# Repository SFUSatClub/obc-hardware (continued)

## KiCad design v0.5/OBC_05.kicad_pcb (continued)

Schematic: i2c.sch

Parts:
R10, R11: 10k; R_0402
U1: TMS570LS0714; LQFP-144_20x20mm_Pitch0.5mm

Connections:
1v2: U1.17, U1.29, U1.45, U1.48, U1.49, U1.57, U1.87, U1.101, U1.114, U1.123, U1.137, U1.143; also elsewhere on the board
3v3: R10.1, R11.1, U1.10, U1.26, U1.42, U1.66, U1.69, U1.104, U1.120, U1.134, U1.136; also elsewhere on the board
/MCU_Support_Reset/OSC_N: U1.20; also elsewhere on the board
/MCU_Support_Reset/OSC_P: U1.18; also elsewhere on the board
AD1_11: U1.75
AD1_12: U1.77
AD1_13: U1.79
AD1_14: U1.82
AD1_15: U1.85
AD1_16: U1.58
AD1_17: U1.59; also elsewhere on the board
AD1_18: U1.62; also elsewhere on the board
AD1_19: U1.63; also elsewhere on the board
AD1_20: U1.64; also elsewhere on the board
AD1_21: U1.65
AD1_22: U1.81
AD1_23: U1.84
FLASH0_CS: U1.105; also elsewhere on the board
FLASH1_CS: U1.130; also elsewhere on the board
FLASH2_CS: U1.40; also elsewhere on the board
FLASH_CLK: U1.95; also elsewhere on the board
FLASH_MISO: U1.94; also elsewhere on the board
FLASH_MOSI: U1.93; also elsewhere on the board
GIOA0: U1.2; also elsewhere on the board
GIOA1: U1.5; also elsewhere on the board
GIOA2: U1.9; also elsewhere on the board
GIOA6: U1.16; also elsewhere on the board
GIOB1: U1.133; also elsewhere on the board
GIOB2: U1.142; also elsewhere on the board
GIOB3: U1.1; also elsewhere on the board
GND: U1.11, U1.21, U1.27, U1.28, U1.34, U1.43, U1.44, U1.47, U1.50, U1.56, U1.67, U1.68, U1.88, U1.102, U1.103, U1.115, U1.121, U1.122, U1.135, U1.138, U1.144; also elsewhere on the board
I2C_SCL: R11.2, U1.3; also elsewhere on the board
I2C_SDA: R10.2, U1.4; also elsewhere on the board
INA_OUT: U1.73; also elsewhere on the board
LIN_RX: U1.131; also elsewhere on the board
LIN_TX: U1.132; also elsewhere on the board
MASTER_RESET: U1.46; also elsewhere on the board
unnamed 43: U1.19; also elsewhere on the board
unnamed 46: U1.116; also elsewhere on the board
unnamed 104: U1.55; also elsewhere on the board
unnamed 115: U1.86; also elsewhere on the board
RF_CLK: U1.53; also elsewhere on the board
RF_CS: U1.37; also elsewhere on the board
RF_CS2: U1.6; also elsewhere on the board
RF_IRQ: U1.14; also elsewhere on the board
RF_MISO: U1.51; also elsewhere on the board
RF_MOSI: U1.52; also elsewhere on the board
RTCK: U1.113
RTC_CLK: U1.100; also elsewhere on the board
RTC_CS: U1.32; also elsewhere on the board
RTC_MISO: U1.98; also elsewhere on the board
RTC_MOSI: U1.99; also elsewhere on the board
TCK: U1.112; also elsewhere on the board
TDI: U1.110; also elsewhere on the board
TDO: U1.111; also elsewhere on the board
TMS: U1.108; also elsewhere on the board
UART_RX: U1.38; also elsewhere on the board
UART_TX: U1.39; also elsewhere on the board
WATCHDOG: U1.126; also elsewhere on the board
nERROR: U1.117; also elsewhere on the board
nTRST: U1.109; also elsewhere on the board
xGPIO0: U1.23; also elsewhere on the board
xGPIO1: U1.30; also elsewhere on the board
xGPIO2: U1.31; also elsewhere on the board
xGPIO3: U1.97; also elsewhere on the board
xGPIO4: U1.96; also elsewhere on the board
xGPIO5: U1.91; also elsewhere on the board
xGPIO6: U1.41; also elsewhere on the board
xGPIO7: U1.22; also elsewhere on the board
xGPIO8: U1.106; also elsewhere on the board
xGPIO9: U1.90; also elsewhere on the board
xGPIO10: U1.89; also elsewhere on the board
xGPIO11: U1.129; also elsewhere on the board
xGPIO12: U1.128; also elsewhere on the board
xNHET0: U1.15; also elsewhere on the board
xNHET1: U1.92; also elsewhere on the board

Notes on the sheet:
I2C pullup resistor values are hotly contested. Temp sensor datasheet says 10k, this has been tested and works with 0.4. May need to adjust once more devices are on the bus.

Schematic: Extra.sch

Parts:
U1: TMS570LS0714; LQFP-144_20x20mm_Pitch0.5mm

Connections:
1v2: U1.17, U1.29, U1.45, U1.48, U1.49, U1.57, U1.87, U1.101, U1.114, U1.123, U1.137, U1.143; also elsewhere on the board
3v3: U1.10, U1.26, U1.42, U1.66, U1.69, U1.104, U1.120, U1.134, U1.136; also elsewhere on the board
/MCU_Support_Reset/OSC_N: U1.20; also elsewhere on the board
/MCU_Support_Reset/OSC_P: U1.18; also elsewhere on the board
AD1_11: U1.75
AD1_12: U1.77
AD1_13: U1.79
AD1_14: U1.82
AD1_15: U1.85
AD1_16: U1.58
AD1_17: U1.59; also elsewhere on the board
AD1_18: U1.62; also elsewhere on the board
AD1_19: U1.63; also elsewhere on the board
AD1_20: U1.64; also elsewhere on the board
AD1_21: U1.65
AD1_22: U1.81
AD1_23: U1.84
FLASH0_CS: U1.105; also elsewhere on the board
FLASH1_CS: U1.130; also elsewhere on the board
FLASH2_CS: U1.40; also elsewhere on the board
FLASH_CLK: U1.95; also elsewhere on the board
FLASH_MISO: U1.94; also elsewhere on the board
FLASH_MOSI: U1.93; also elsewhere on the board
GIOA0: U1.2; also elsewhere on the board
GIOA1: U1.5; also elsewhere on the board
GIOA2: U1.9; also elsewhere on the board
GIOA6: U1.16; also elsewhere on the board
GIOB1: U1.133; also elsewhere on the board
GIOB2: U1.142; also elsewhere on the board
GIOB3: U1.1; also elsewhere on the board
GND: U1.11, U1.21, U1.27, U1.28, U1.34, U1.43, U1.44, U1.47, U1.50, U1.56, U1.67, U1.68, U1.88, U1.102, U1.103, U1.115, U1.121, U1.122, U1.135, U1.138, U1.144; also elsewhere on the board
I2C_SCL: U1.3; also elsewhere on the board
I2C_SDA: U1.4; also elsewhere on the board
INA_OUT: U1.73; also elsewhere on the board
LIN_RX: U1.131; also elsewhere on the board
LIN_TX: U1.132; also elsewhere on the board
MASTER_RESET: U1.46; also elsewhere on the board
unnamed 43: U1.19; also elsewhere on the board
unnamed 46: U1.116; also elsewhere on the board
unnamed 104: U1.55; also elsewhere on the board
unnamed 115: U1.86; also elsewhere on the board
RF_CLK: U1.53; also elsewhere on the board
RF_CS: U1.37; also elsewhere on the board
RF_CS2: U1.6; also elsewhere on the board
RF_IRQ: U1.14; also elsewhere on the board
RF_MISO: U1.51; also elsewhere on the board
RF_MOSI: U1.52; also elsewhere on the board
RTCK: U1.113
RTC_CLK: U1.100; also elsewhere on the board
RTC_CS: U1.32; also elsewhere on the board
RTC_MISO: U1.98; also elsewhere on the board
RTC_MOSI: U1.99; also elsewhere on the board
TCK: U1.112; also elsewhere on the board
TDI: U1.110; also elsewhere on the board
TDO: U1.111; also elsewhere on the board
TMS: U1.108; also elsewhere on the board
UART_RX: U1.38; also elsewhere on the board
UART_TX: U1.39; also elsewhere on the board
WATCHDOG: U1.126; also elsewhere on the board
nERROR: U1.117; also elsewhere on the board
nTRST: U1.109; also elsewhere on the board
xGPIO0: U1.23; also elsewhere on the board
xGPIO1: U1.30; also elsewhere on the board
xGPIO2: U1.31; also elsewhere on the board
xGPIO3: U1.97; also elsewhere on the board
xGPIO4: U1.96; also elsewhere on the board
xGPIO5: U1.91; also elsewhere on the board
xGPIO6: U1.41; also elsewhere on the board
xGPIO7: U1.22; also elsewhere on the board
xGPIO8: U1.106; also elsewhere on the board
xGPIO9: U1.90; also elsewhere on the board
xGPIO10: U1.89; also elsewhere on the board
xGPIO11: U1.129; also elsewhere on the board
xGPIO12: U1.128; also elsewhere on the board
xNHET0: U1.15; also elsewhere on the board
xNHET1: U1.92; also elsewhere on the board

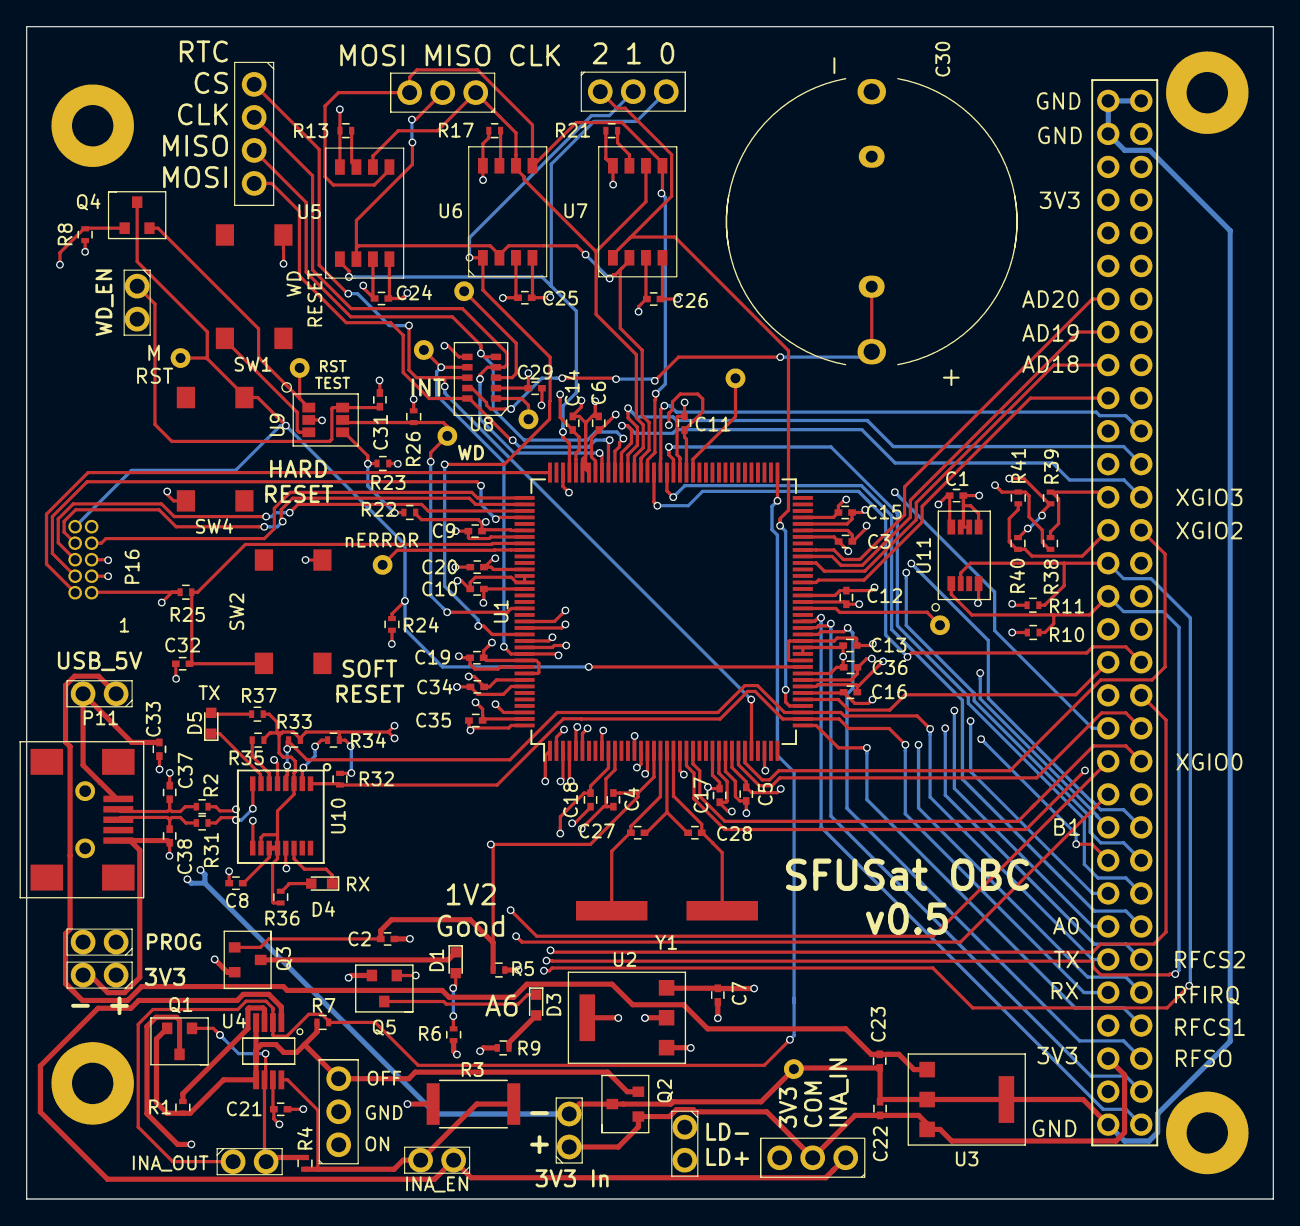
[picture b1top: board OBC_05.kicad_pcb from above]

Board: 4 copper layers, 95.9 x 90.2 mm, 118 parts (0 on the bottom side), 103 nets.

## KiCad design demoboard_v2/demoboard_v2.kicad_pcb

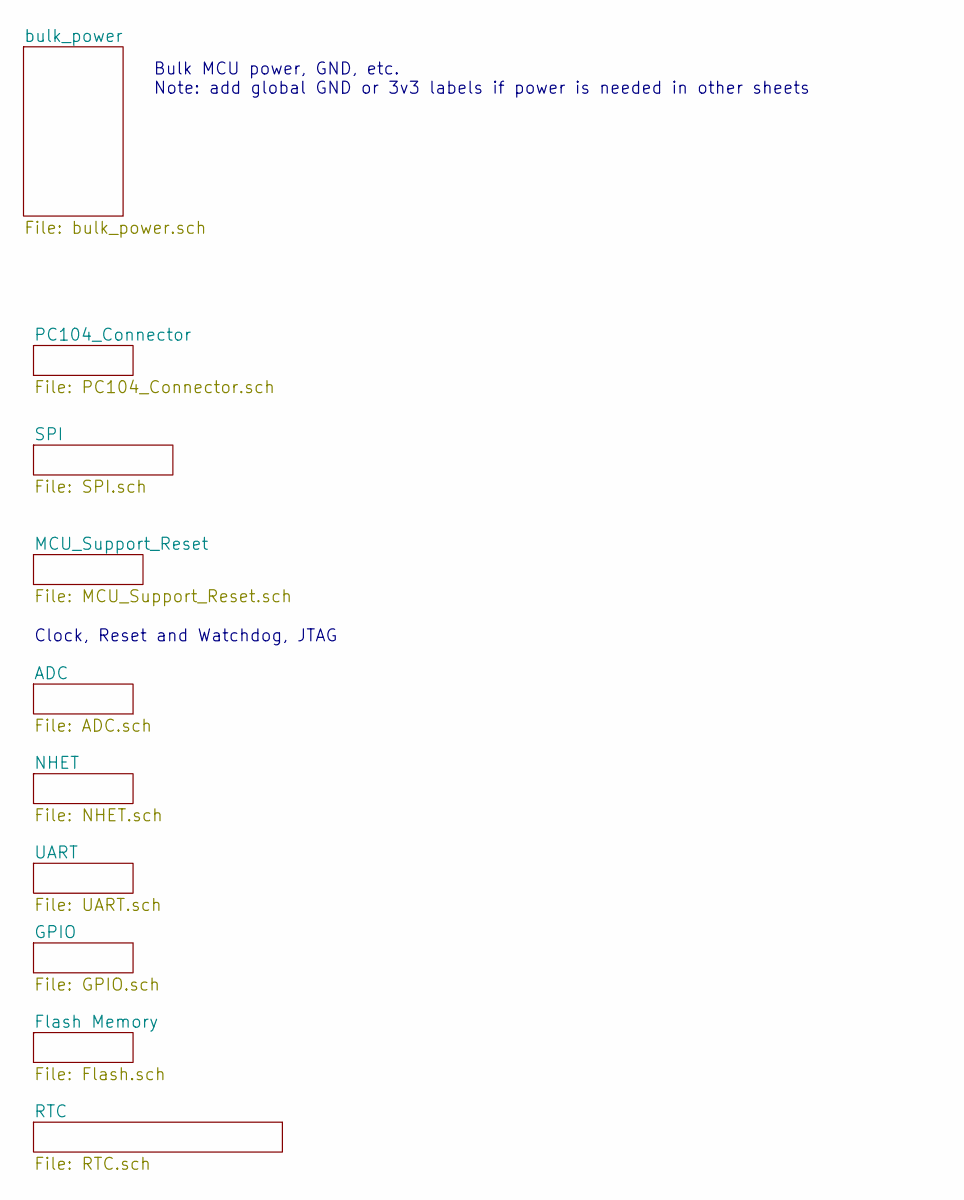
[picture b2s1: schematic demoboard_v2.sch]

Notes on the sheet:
Clock, Reset and Watchdog, JTAG
Bulk MCU power, GND, etc. Note: add global GND or 3v3 labels if power is needed in other sheets

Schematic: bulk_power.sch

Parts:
C2: 1uF; C_0402
C4, C5, C6, C7, C9, C10, C11, C12, C13, C14, C15, C16, C17, C18, C19, C20: 0.1µF; C_0402
C21, C23: 1µF; C_0402
C22: 4.7µF; C_0402
D1: LED; LED_0603
P1: 3v3_IN_CONNECTOR; 2x01In_Header_v2
P2: INA_INPUT; 3x_01In_Header_v2
P3: INA_GND; 3x_01In_Header_v2
P4: INA_EN; 2x01In_Header_v2
P5: INA_OUTPUT; 2x01In_Header_v2
Q1, Q2: DMN2075U; SOT23_DMN2075U
Q3: 1v2_GOOD; SOT23_DMN2075U
R1: 2k; R_0402
R2, R4: 10k; R_0402
R3: 0.04; R_2512
R5: 10K; R_0402
R6: 100; R_0402
U1: TMS570LS0714; LQFP-144_20x20mm_Pitch0.5mm
U2: AP7331; SOT25
U3: AP7361_3.3v; SOT-223
U4: INA301; VSSOP_8

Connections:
1v2: C2.1, C4.1, C5.1, C6.1, C7.1, C9.1, C10.1, C11.1, C12.1, C13.1, Q3.2 (G), R5.1, U1.17, U1.29, U1.45, U1.48, U1.49, U1.57, U1.87, U1.101, U1.114, U1.123, U1.137, U1.143, U2.5 (OUT); also elsewhere on the board
3v3: C14.2, C15.1, C16.1, C17.2, C18.1, C19.1, C20.1, C21.1, P1.1, P2.3, Q2.2 (G), R3.2, R6.1, U1.10, U1.26, U1.42, U1.66, U1.69, U1.104, U1.120, U1.134, U1.136, U2.1 (IN), U2.3 (EN), U4.7 (IN-); also elsewhere on the board
3v3_OUTPUT: C22.1, P2.2, U3.3
5v0: C23.1, U3.1; also elsewhere on the board
104_GND: C22.2, C23.2, P3.3, Q1.3 (S), R2.2, U3.2, U3.4, U4.4 (GND), U4.5 (RESET); also elsewhere on the board
AD1_3: U1.74; also elsewhere on the board
AD1_4: U1.76; also elsewhere on the board
AD1_5: U1.78; also elsewhere on the board
AD1_6: U1.80; also elsewhere on the board
AD1_7: U1.61; also elsewhere on the board
AD1_8: U1.83; also elsewhere on the board
AD1_9: U1.70; also elsewhere on the board
AD1_10: U1.72; also elsewhere on the board
FLASH0_CS: U1.105; also elsewhere on the board
FLASH1_CS: U1.130; also elsewhere on the board
FLASH2_CS: U1.40; also elsewhere on the board
FLASH_CLK: U1.95; also elsewhere on the board
FLASH_MISO: U1.94; also elsewhere on the board
FLASH_MOSI: U1.93; also elsewhere on the board
GIOA0: U1.2; also elsewhere on the board
GIOA1: U1.5
GIOA2: U1.9
GIOA6: U1.16; also elsewhere on the board
GIOA7: U1.22
GIOB1: U1.133; also elsewhere on the board
GIOB2: U1.142; also elsewhere on the board
GIOB3: U1.1; also elsewhere on the board
GND: C2.2, C4.2, C5.2, C6.2, C7.2, C9.2, C10.2, C11.2, C12.2, C13.2, C14.1, C15.2, C16.2, C17.1, C18.2, C19.2, C20.2, C21.2, P3.2, Q2.3 (S), Q3.3 (S), R5.2, U1.11, U1.21, U1.27, U1.28, U1.34, U1.43, U1.44, U1.47, U1.50, U1.56, U1.67, U1.68, U1.88, U1.102, U1.103, U1.115, U1.121, U1.122, U1.135, U1.138, U1.144, U2.2 (GND); also elsewhere on the board
I2C_SCL: U1.3; also elsewhere on the board
I2C_SDA: U1.4; also elsewhere on the board
INA_ALERT: P5.2, Q1.2 (G), R4.2, U4.6 (ALERT)
INA_INPUT: P2.1, P4.1, U4.1 (VS)
INA_OUT: P5.1, U1.73, U4.2 (OUT); also elsewhere on the board
MASTER_RESET: U1.46; also elsewhere on the board
NHET1_4: U1.36; also elsewhere on the board
NHET1_7: U1.33; also elsewhere on the board
NHET1_22: U1.15; also elsewhere on the board
NHET1_26: U1.92; also elsewhere on the board
unnamed 40: U1.19; also elsewhere on the board
unnamed 41: U1.18; also elsewhere on the board
unnamed 42: U1.20; also elsewhere on the board
unnamed 44: U1.116; also elsewhere on the board
unnamed: D1.1, Q3.1 (D)
unnamed: D1.2, R6.2
unnamed: P1.2, Q2.1 (D)
unnamed: P3.1, Q1.1 (D)
unnamed: P4.2, R3.1, R4.1, U4.8 (IN+)
unnamed: R1.1, U4.3 (LIMIT)
unnamed: R1.2, R2.1
unnamed 86: U1.97; also elsewhere on the board
unnamed 93: U1.55; also elsewhere on the board
unnamed 107: U1.86; also elsewhere on the board
unnamed 112: U1.117; also elsewhere on the board
RF_ADC1: U1.60; also elsewhere on the board
RF_ADC2: U1.71; also elsewhere on the board
RF_CLK: U1.53; also elsewhere on the board
RF_CS: U1.37; also elsewhere on the board
RF_GAIN_CS: U1.6; also elsewhere on the board
RF_MISO: U1.51; also elsewhere on the board
RF_MOSI: U1.52; also elsewhere on the board
RF_PWM1: U1.140; also elsewhere on the board
RF_PWM2: U1.141; also elsewhere on the board
RTCK: U1.113; also elsewhere on the board
RTC_CLK: U1.25; also elsewhere on the board
RTC_CS: U1.24; also elsewhere on the board
RTC_MISO: U1.31; also elsewhere on the board
RTC_MOSI: U1.30; also elsewhere on the board
SPI5_CLK: U1.100; also elsewhere on the board
SPI5_CS0: U1.32; also elsewhere on the board
SPI5_MISO: U1.98; also elsewhere on the board
SPI5_MOSI: U1.99; also elsewhere on the board
TCK: U1.112; also elsewhere on the board
TDI: U1.110; also elsewhere on the board
TDO: U1.111; also elsewhere on the board
TMS: U1.108; also elsewhere on the board
UART_RX: U1.38; also elsewhere on the board
UART_TX: U1.39; also elsewhere on the board
WATCHDOG: U1.126; also elsewhere on the board
nTRST: U1.109; also elsewhere on the board

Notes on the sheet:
1.2v regulator
INA_POWER_ENABLE Short this connector if using INA Prevents INA from being powered when it is supposed to be disconnected
Use this connector to enable or disable INA control
2+3 closed: INA Disabled 2+1 closed: INA Enabled
reverse polarity fet
SEL Protection FET
C1, C3, C8 were removed at the board level, as multiple pins were connected to one cap.

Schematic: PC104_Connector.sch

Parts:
D2: PESD5Zx; PESD57zx
J1: PC104-8BIT; PC104-8bit
Q4: DMN2075U; SOT23_DMN2075U

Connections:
5v0: D2.1 (c), J1.3B, J1.29B, Q4.2 (G); also elsewhere on the board
104_GND: Q4.3 (S); also elsewhere on the board
104_In_GND: D2.2 (a), J1.1B, J1.31B, J1.32A, J1.32B, Q4.1 (D)
AD1_3: J1.19A; also elsewhere on the board
AD1_4: J1.20A; also elsewhere on the board
AD1_5: J1.21A; also elsewhere on the board
AD1_6: J1.22A; also elsewhere on the board
AD1_7: J1.23A; also elsewhere on the board
AD1_8: J1.24A; also elsewhere on the board
AD1_9: J1.25A; also elsewhere on the board
AD1_10: J1.26A; also elsewhere on the board
ANTENNA_DEPLOY: J1.7A
GIOA0: J1.7B; also elsewhere on the board
GIOB1: J1.8B; also elsewhere on the board
GIOB2: J1.11B; also elsewhere on the board
GIOB3: J1.12B; also elsewhere on the board
I2C_SCL: J1.18B; also elsewhere on the board
I2C_SDA: J1.17B; also elsewhere on the board
NHET1_4: J1.19B; also elsewhere on the board
NHET1_7: J1.20B; also elsewhere on the board
NHET1_22: J1.21B; also elsewhere on the board
NHET1_26: J1.22B; also elsewhere on the board
RF_ADC1: J1.8A; also elsewhere on the board
RF_ADC2: J1.9A; also elsewhere on the board
RF_CLK: J1.1A; also elsewhere on the board
RF_CS: J1.4A; also elsewhere on the board
RF_GAIN_CS: J1.6A; also elsewhere on the board
RF_IRQ: J1.5A
RF_MISO: J1.3A; also elsewhere on the board
RF_MOSI: J1.2A; also elsewhere on the board
RF_PWM1: J1.10A; also elsewhere on the board
RF_PWM2: J1.11A; also elsewhere on the board
SPI5_CLK: J1.16A; also elsewhere on the board
SPI5_CS0: J1.17A; also elsewhere on the board
SPI5_MISO: J1.14A; also elsewhere on the board
SPI5_MOSI: J1.15A; also elsewhere on the board
UART_RX: J1.5B; also elsewhere on the board
UART_TX: J1.6B; also elsewhere on the board

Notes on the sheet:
Global Power Needed to connect power on the different sheets
Grounding: 104_GND is connected either to "GND" net directly, or to GND net through the FET, allowing the load to be switched by the SEL mitigation circuit. This is selected by a jumper on the power page.
5v reverse polarity FET

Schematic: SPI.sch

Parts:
U1: TMS570LS0714; LQFP-144_20x20mm_Pitch0.5mm

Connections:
1v2: U1.17, U1.29, U1.45, U1.48, U1.49, U1.57, U1.87, U1.101, U1.114, U1.123, U1.137, U1.143; also elsewhere on the board
3v3: U1.10, U1.26, U1.42, U1.66, U1.69, U1.104, U1.120, U1.134, U1.136; also elsewhere on the board
AD1_3: U1.74; also elsewhere on the board
AD1_4: U1.76; also elsewhere on the board
AD1_5: U1.78; also elsewhere on the board
AD1_6: U1.80; also elsewhere on the board
AD1_7: U1.61; also elsewhere on the board
AD1_8: U1.83; also elsewhere on the board
AD1_9: U1.70; also elsewhere on the board
AD1_10: U1.72; also elsewhere on the board
FLASH0_CS: U1.105; also elsewhere on the board
FLASH1_CS: U1.130; also elsewhere on the board
FLASH2_CS: U1.40; also elsewhere on the board
FLASH_CLK: U1.95; also elsewhere on the board
FLASH_MISO: U1.94; also elsewhere on the board
FLASH_MOSI: U1.93; also elsewhere on the board
GIOA0: U1.2; also elsewhere on the board
GIOA1: U1.5
GIOA2: U1.9
GIOA6: U1.16; also elsewhere on the board
GIOA7: U1.22
GIOB1: U1.133; also elsewhere on the board
GIOB2: U1.142; also elsewhere on the board
GIOB3: U1.1; also elsewhere on the board
GND: U1.11, U1.21, U1.27, U1.28, U1.34, U1.43, U1.44, U1.47, U1.50, U1.56, U1.67, U1.68, U1.88, U1.102, U1.103, U1.115, U1.121, U1.122, U1.135, U1.138, U1.144; also elsewhere on the board
I2C_SCL: U1.3; also elsewhere on the board
I2C_SDA: U1.4; also elsewhere on the board
INA_OUT: U1.73; also elsewhere on the board
MASTER_RESET: U1.46; also elsewhere on the board
NHET1_4: U1.36; also elsewhere on the board
NHET1_7: U1.33; also elsewhere on the board
NHET1_22: U1.15; also elsewhere on the board
NHET1_26: U1.92; also elsewhere on the board
unnamed 40: U1.19; also elsewhere on the board
unnamed 41: U1.18; also elsewhere on the board
unnamed 42: U1.20; also elsewhere on the board
unnamed 44: U1.116; also elsewhere on the board
unnamed 86: U1.97; also elsewhere on the board
unnamed 93: U1.55; also elsewhere on the board
unnamed 107: U1.86; also elsewhere on the board
unnamed 112: U1.117; also elsewhere on the board
RF_ADC1: U1.60; also elsewhere on the board
RF_ADC2: U1.71; also elsewhere on the board
RF_CLK: U1.53; also elsewhere on the board
RF_CS: U1.37; also elsewhere on the board
RF_GAIN_CS: U1.6; also elsewhere on the board
RF_MISO: U1.51; also elsewhere on the board
RF_MOSI: U1.52; also elsewhere on the board
RF_PWM1: U1.140; also elsewhere on the board
RF_PWM2: U1.141; also elsewhere on the board
RTCK: U1.113; also elsewhere on the board
RTC_CLK: U1.25; also elsewhere on the board
RTC_CS: U1.24; also elsewhere on the board
RTC_MISO: U1.31; also elsewhere on the board
RTC_MOSI: U1.30; also elsewhere on the board
SPI5_CLK: U1.100; also elsewhere on the board
SPI5_CS0: U1.32; also elsewhere on the board
SPI5_MISO: U1.98; also elsewhere on the board
SPI5_MOSI: U1.99; also elsewhere on the board
TCK: U1.112; also elsewhere on the board
TDI: U1.110; also elsewhere on the board
TDO: U1.111; also elsewhere on the board
TMS: U1.108; also elsewhere on the board
UART_RX: U1.38; also elsewhere on the board
UART_TX: U1.39; also elsewhere on the board
WATCHDOG: U1.126; also elsewhere on the board
nTRST: U1.109; also elsewhere on the board

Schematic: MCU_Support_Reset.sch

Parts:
C27, C28: 33pF; C_0402
C31, C32: 0.1µF; C_0402
JTAG_5V_SRC1: JTAG_5V_SRC; 2x01In_Header_v2
P7: OSC_FUALT_INJECT; 2x01In_Header_v2
P12: JTAG_20PIN; JTAG_20pin
R22: 200k; R_0402
R23: 187k; R_0402
R24, R27, R28, R29, R30: 100k; R_0402
R25: 10k; R_0402
SW1, SW2: SPST; Tact_SW_SMD_v2
U1: TMS570LS0714; LQFP-144_20x20mm_Pitch0.5mm
U9: TPS3110; SOT_23_6
W12: nERROR; Test_Point
W14: RESET_TEST; Test_Point
Y1: XTAL; SMD_XTAL

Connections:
1v2: R22.1, U1.17, U1.29, U1.45, U1.48, U1.49, U1.57, U1.87, U1.101, U1.114, U1.123, U1.137, U1.143; also elsewhere on the board
3v3: C31.1, P12.1, R24.1, R25.1, R27.1, R28.1, R29.1, R30.1, U1.10, U1.26, U1.42, U1.66, U1.69, U1.104, U1.120, U1.134, U1.136, U9.6 (VDD); also elsewhere on the board
5v0: JTAG_5V_SRC1.2; also elsewhere on the board
AD1_3: U1.74; also elsewhere on the board
AD1_4: U1.76; also elsewhere on the board
AD1_5: U1.78; also elsewhere on the board
AD1_6: U1.80; also elsewhere on the board
AD1_7: U1.61; also elsewhere on the board
AD1_8: U1.83; also elsewhere on the board
AD1_9: U1.70; also elsewhere on the board
AD1_10: U1.72; also elsewhere on the board
FLASH0_CS: U1.105; also elsewhere on the board
FLASH1_CS: U1.130; also elsewhere on the board
FLASH2_CS: U1.40; also elsewhere on the board
FLASH_CLK: U1.95; also elsewhere on the board
FLASH_MISO: U1.94; also elsewhere on the board
FLASH_MOSI: U1.93; also elsewhere on the board
GIOA0: U1.2; also elsewhere on the board
GIOA1: U1.5
GIOA2: U1.9
GIOA6: U1.16; also elsewhere on the board
GIOA7: U1.22
GIOB1: U1.133; also elsewhere on the board
GIOB2: U1.142; also elsewhere on the board
GIOB3: U1.1; also elsewhere on the board
GND: C31.2, C32.2, P7.1, P12.4, P12.6, P12.8, P12.10, P12.12, P12.14, P12.16, P12.18, P12.20, R23.2, SW1.2, SW2.2, U1.11, U1.21, U1.27, U1.28, U1.34, U1.43, U1.44, U1.47, U1.50, U1.56, U1.67, U1.68, U1.88, U1.102, U1.103, U1.115, U1.121, U1.122, U1.135, U1.138, U1.144, U9.2 (GND); also elsewhere on the board
I2C_SCL: U1.3; also elsewhere on the board
I2C_SDA: U1.4; also elsewhere on the board
INA_OUT: U1.73; also elsewhere on the board
MASTER_RESET: R24.2, U1.46, U9.1 (RESET), W14.1; also elsewhere on the board
NHET1_4: U1.36; also elsewhere on the board
NHET1_7: U1.33; also elsewhere on the board
NHET1_22: U1.15; also elsewhere on the board
NHET1_26: U1.92; also elsewhere on the board
unnamed: C27.1, C28.1, P7.2, U1.19, Y1.1, Y1.2
unnamed: C27.2, U1.18
unnamed: C28.2, U1.20
unnamed: C32.1, R25.2, SW2.1, U1.116
unnamed: JTAG_5V_SRC1.1, P12.19
unnamed: R22.2, R23.1, U9.4 (SENSE)
unnamed 86: U1.97; also elsewhere on the board
unnamed: SW1.1, U9.3 (MR)
unnamed 93: U1.55; also elsewhere on the board
unnamed 107: U1.86; also elsewhere on the board
unnamed: U1.117, W12.1
RF_ADC1: U1.60; also elsewhere on the board
RF_ADC2: U1.71; also elsewhere on the board
RF_CLK: U1.53; also elsewhere on the board
RF_CS: U1.37; also elsewhere on the board
RF_GAIN_CS: U1.6; also elsewhere on the board
RF_MISO: U1.51; also elsewhere on the board
RF_MOSI: U1.52; also elsewhere on the board
RF_PWM1: U1.140; also elsewhere on the board
RF_PWM2: U1.141; also elsewhere on the board
RTCK: P12.11, R28.2, U1.113
RTC_CLK: U1.25; also elsewhere on the board
RTC_CS: U1.24; also elsewhere on the board
RTC_MISO: U1.31; also elsewhere on the board
RTC_MOSI: U1.30; also elsewhere on the board
SPI5_CLK: U1.100; also elsewhere on the board
SPI5_CS0: U1.32; also elsewhere on the board
SPI5_MISO: U1.98; also elsewhere on the board
SPI5_MOSI: U1.99; also elsewhere on the board
TCK: P12.9, R27.2, U1.112
TDI: P12.5, R29.2, U1.110
TDO: P12.13, U1.111
TMS: P12.7, R30.2, U1.108
UART_RX: U1.38; also elsewhere on the board
UART_TX: U1.39; also elsewhere on the board
WATCHDOG: U1.126, U9.5 (WDI); also elsewhere on the board
nTRST: P12.3, U1.109

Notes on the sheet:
nPORRST is hard reset
Soft Reset
Hard reset switch.

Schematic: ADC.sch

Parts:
R7: 10k; R_0402
U1: TMS570LS0714; LQFP-144_20x20mm_Pitch0.5mm
W7: AD1EVT1; Test_Point
W8: GIOB2; Test_Point

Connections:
1v2: U1.17, U1.29, U1.45, U1.48, U1.49, U1.57, U1.87, U1.101, U1.114, U1.123, U1.137, U1.143; also elsewhere on the board
3v3: U1.10, U1.26, U1.42, U1.66, U1.69, U1.104, U1.120, U1.134, U1.136; also elsewhere on the board
104_GND: R7.2; also elsewhere on the board
AD1_3: U1.74; also elsewhere on the board
AD1_4: U1.76; also elsewhere on the board
AD1_5: U1.78; also elsewhere on the board
AD1_6: U1.80; also elsewhere on the board
AD1_7: U1.61; also elsewhere on the board
AD1_8: U1.83; also elsewhere on the board
AD1_9: U1.70; also elsewhere on the board
AD1_10: U1.72; also elsewhere on the board
FLASH0_CS: U1.105; also elsewhere on the board
FLASH1_CS: U1.130; also elsewhere on the board
FLASH2_CS: U1.40; also elsewhere on the board
FLASH_CLK: U1.95; also elsewhere on the board
FLASH_MISO: U1.94; also elsewhere on the board
FLASH_MOSI: U1.93; also elsewhere on the board
GIOA0: U1.2; also elsewhere on the board
GIOA1: U1.5
GIOA2: U1.9
GIOA6: U1.16; also elsewhere on the board
GIOA7: U1.22
GIOB1: U1.133; also elsewhere on the board
GIOB2: U1.142; also elsewhere on the board
GIOB3: U1.1; also elsewhere on the board
GND: U1.11, U1.21, U1.27, U1.28, U1.34, U1.43, U1.44, U1.47, U1.50, U1.56, U1.67, U1.68, U1.88, U1.102, U1.103, U1.115, U1.121, U1.122, U1.135, U1.138, U1.144; also elsewhere on the board
I2C_SCL: U1.3; also elsewhere on the board
I2C_SDA: U1.4; also elsewhere on the board
INA_OUT: R7.1, U1.73; also elsewhere on the board
MASTER_RESET: U1.46; also elsewhere on the board
NHET1_4: U1.36; also elsewhere on the board
NHET1_7: U1.33; also elsewhere on the board
NHET1_22: U1.15; also elsewhere on the board
NHET1_26: U1.92; also elsewhere on the board
unnamed 40: U1.19; also elsewhere on the board
unnamed 41: U1.18; also elsewhere on the board
unnamed 42: U1.20; also elsewhere on the board
unnamed 44: U1.116; also elsewhere on the board
unnamed 86: U1.97; also elsewhere on the board
unnamed: U1.55, W8.1
unnamed: U1.86, W7.1
unnamed 112: U1.117; also elsewhere on the board
RF_ADC1: U1.60; also elsewhere on the board
RF_ADC2: U1.71; also elsewhere on the board
RF_CLK: U1.53; also elsewhere on the board
RF_CS: U1.37; also elsewhere on the board
RF_GAIN_CS: U1.6; also elsewhere on the board
RF_MISO: U1.51; also elsewhere on the board
RF_MOSI: U1.52; also elsewhere on the board
RF_PWM1: U1.140; also elsewhere on the board
RF_PWM2: U1.141; also elsewhere on the board
RTCK: U1.113; also elsewhere on the board
RTC_CLK: U1.25; also elsewhere on the board
RTC_CS: U1.24; also elsewhere on the board
RTC_MISO: U1.31; also elsewhere on the board
RTC_MOSI: U1.30; also elsewhere on the board
SPI5_CLK: U1.100; also elsewhere on the board
SPI5_CS0: U1.32; also elsewhere on the board
SPI5_MISO: U1.98; also elsewhere on the board
SPI5_MOSI: U1.99; also elsewhere on the board
TCK: U1.112; also elsewhere on the board
TDI: U1.110; also elsewhere on the board
TDO: U1.111; also elsewhere on the board
TMS: U1.108; also elsewhere on the board
UART_RX: U1.38; also elsewhere on the board
UART_TX: U1.39; also elsewhere on the board
WATCHDOG: U1.126; also elsewhere on the board
nTRST: U1.109; also elsewhere on the board

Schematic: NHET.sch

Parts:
U1: TMS570LS0714; LQFP-144_20x20mm_Pitch0.5mm

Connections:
1v2: U1.17, U1.29, U1.45, U1.48, U1.49, U1.57, U1.87, U1.101, U1.114, U1.123, U1.137, U1.143; also elsewhere on the board
3v3: U1.10, U1.26, U1.42, U1.66, U1.69, U1.104, U1.120, U1.134, U1.136; also elsewhere on the board
AD1_3: U1.74; also elsewhere on the board
AD1_4: U1.76; also elsewhere on the board
AD1_5: U1.78; also elsewhere on the board
AD1_6: U1.80; also elsewhere on the board
AD1_7: U1.61; also elsewhere on the board
AD1_8: U1.83; also elsewhere on the board
AD1_9: U1.70; also elsewhere on the board
AD1_10: U1.72; also elsewhere on the board
FLASH0_CS: U1.105; also elsewhere on the board
FLASH1_CS: U1.130; also elsewhere on the board
FLASH2_CS: U1.40; also elsewhere on the board
FLASH_CLK: U1.95; also elsewhere on the board
FLASH_MISO: U1.94; also elsewhere on the board
FLASH_MOSI: U1.93; also elsewhere on the board
GIOA0: U1.2; also elsewhere on the board
GIOA1: U1.5
GIOA2: U1.9
GIOA6: U1.16; also elsewhere on the board
GIOA7: U1.22
GIOB1: U1.133; also elsewhere on the board
GIOB2: U1.142; also elsewhere on the board
GIOB3: U1.1; also elsewhere on the board
GND: U1.11, U1.21, U1.27, U1.28, U1.34, U1.43, U1.44, U1.47, U1.50, U1.56, U1.67, U1.68, U1.88, U1.102, U1.103, U1.115, U1.121, U1.122, U1.135, U1.138, U1.144; also elsewhere on the board
I2C_SCL: U1.3; also elsewhere on the board
I2C_SDA: U1.4; also elsewhere on the board
INA_OUT: U1.73; also elsewhere on the board
MASTER_RESET: U1.46; also elsewhere on the board
NHET1_4: U1.36; also elsewhere on the board
NHET1_7: U1.33; also elsewhere on the board
NHET1_22: U1.15; also elsewhere on the board
NHET1_26: U1.92; also elsewhere on the board
unnamed 40: U1.19; also elsewhere on the board
unnamed 41: U1.18; also elsewhere on the board
unnamed 42: U1.20; also elsewhere on the board
unnamed 44: U1.116; also elsewhere on the board
unnamed 86: U1.97; also elsewhere on the board
unnamed 93: U1.55; also elsewhere on the board
unnamed 107: U1.86; also elsewhere on the board
unnamed 112: U1.117; also elsewhere on the board
RF_ADC1: U1.60; also elsewhere on the board
RF_ADC2: U1.71; also elsewhere on the board
RF_CLK: U1.53; also elsewhere on the board
RF_CS: U1.37; also elsewhere on the board
RF_GAIN_CS: U1.6; also elsewhere on the board
RF_MISO: U1.51; also elsewhere on the board
RF_MOSI: U1.52; also elsewhere on the board
RF_PWM1: U1.140; also elsewhere on the board
RF_PWM2: U1.141; also elsewhere on the board
RTCK: U1.113; also elsewhere on the board
RTC_CLK: U1.25; also elsewhere on the board
RTC_CS: U1.24; also elsewhere on the board
RTC_MISO: U1.31; also elsewhere on the board
RTC_MOSI: U1.30; also elsewhere on the board
SPI5_CLK: U1.100; also elsewhere on the board
SPI5_CS0: U1.32; also elsewhere on the board
SPI5_MISO: U1.98; also elsewhere on the board
SPI5_MOSI: U1.99; also elsewhere on the board
TCK: U1.112; also elsewhere on the board
TDI: U1.110; also elsewhere on the board
TDO: U1.111; also elsewhere on the board
TMS: U1.108; also elsewhere on the board
UART_RX: U1.38; also elsewhere on the board
UART_TX: U1.39; also elsewhere on the board
WATCHDOG: U1.126; also elsewhere on the board
nTRST: U1.109; also elsewhere on the board

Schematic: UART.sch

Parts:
P6: UART; 2x01In_Header_v2
U1: TMS570LS0714; LQFP-144_20x20mm_Pitch0.5mm

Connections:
1v2: U1.17, U1.29, U1.45, U1.48, U1.49, U1.57, U1.87, U1.101, U1.114, U1.123, U1.137, U1.143; also elsewhere on the board
3v3: U1.10, U1.26, U1.42, U1.66, U1.69, U1.104, U1.120, U1.134, U1.136; also elsewhere on the board
AD1_3: U1.74; also elsewhere on the board
AD1_4: U1.76; also elsewhere on the board
AD1_5: U1.78; also elsewhere on the board
AD1_6: U1.80; also elsewhere on the board
AD1_7: U1.61; also elsewhere on the board
AD1_8: U1.83; also elsewhere on the board
AD1_9: U1.70; also elsewhere on the board
AD1_10: U1.72; also elsewhere on the board
FLASH0_CS: U1.105; also elsewhere on the board
FLASH1_CS: U1.130; also elsewhere on the board
FLASH2_CS: U1.40; also elsewhere on the board
FLASH_CLK: U1.95; also elsewhere on the board
FLASH_MISO: U1.94; also elsewhere on the board
FLASH_MOSI: U1.93; also elsewhere on the board
GIOA0: U1.2; also elsewhere on the board
GIOA1: U1.5
GIOA2: U1.9
GIOA6: U1.16; also elsewhere on the board
GIOA7: U1.22
GIOB1: U1.133; also elsewhere on the board
GIOB2: U1.142; also elsewhere on the board
GIOB3: U1.1; also elsewhere on the board
GND: U1.11, U1.21, U1.27, U1.28, U1.34, U1.43, U1.44, U1.47, U1.50, U1.56, U1.67, U1.68, U1.88, U1.102, U1.103, U1.115, U1.121, U1.122, U1.135, U1.138, U1.144; also elsewhere on the board
I2C_SCL: U1.3; also elsewhere on the board
I2C_SDA: U1.4; also elsewhere on the board
INA_OUT: U1.73; also elsewhere on the board
MASTER_RESET: U1.46; also elsewhere on the board
NHET1_4: U1.36; also elsewhere on the board
NHET1_7: U1.33; also elsewhere on the board
NHET1_22: U1.15; also elsewhere on the board
NHET1_26: U1.92; also elsewhere on the board
unnamed 40: U1.19; also elsewhere on the board
unnamed 41: U1.18; also elsewhere on the board
unnamed 42: U1.20; also elsewhere on the board
unnamed 44: U1.116; also elsewhere on the board
unnamed 86: U1.97; also elsewhere on the board
unnamed 93: U1.55; also elsewhere on the board
unnamed 107: U1.86; also elsewhere on the board
unnamed 112: U1.117; also elsewhere on the board
RF_ADC1: U1.60; also elsewhere on the board
RF_ADC2: U1.71; also elsewhere on the board
RF_CLK: U1.53; also elsewhere on the board
RF_CS: U1.37; also elsewhere on the board
RF_GAIN_CS: U1.6; also elsewhere on the board
RF_MISO: U1.51; also elsewhere on the board
RF_MOSI: U1.52; also elsewhere on the board
RF_PWM1: U1.140; also elsewhere on the board
RF_PWM2: U1.141; also elsewhere on the board
RTCK: U1.113; also elsewhere on the board
RTC_CLK: U1.25; also elsewhere on the board
RTC_CS: U1.24; also elsewhere on the board
RTC_MISO: U1.31; also elsewhere on the board
RTC_MOSI: U1.30; also elsewhere on the board
SPI5_CLK: U1.100; also elsewhere on the board
SPI5_CS0: U1.32; also elsewhere on the board
SPI5_MISO: U1.98; also elsewhere on the board
SPI5_MOSI: U1.99; also elsewhere on the board
TCK: U1.112; also elsewhere on the board
TDI: U1.110; also elsewhere on the board
TDO: U1.111; also elsewhere on the board
TMS: U1.108; also elsewhere on the board
UART_RX: U1.38; also elsewhere on the board
UART_TX: U1.39; also elsewhere on the board
WATCHDOG: U1.126; also elsewhere on the board
nTRST: U1.109; also elsewhere on the board
